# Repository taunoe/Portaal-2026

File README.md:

# Portaal

## Hardware

- PCB "Portaal"
- CH32V003F4P6 Board

## PCB "Portaal" Schematics

## Pins

|label|    name|connected|
|-----|--------|---------|
|    G|     GND|      GND|
|    O|Data Out|         |
|    R|        |     3.3V|
|    E|  Enable|      GND|
|    C|   Clock|      PC5|
|    L|    Lach|      PC1|
|    D| Data In|      PC6|
|    +|     VCC|     3.3V|

____
Tauno Erik 2026

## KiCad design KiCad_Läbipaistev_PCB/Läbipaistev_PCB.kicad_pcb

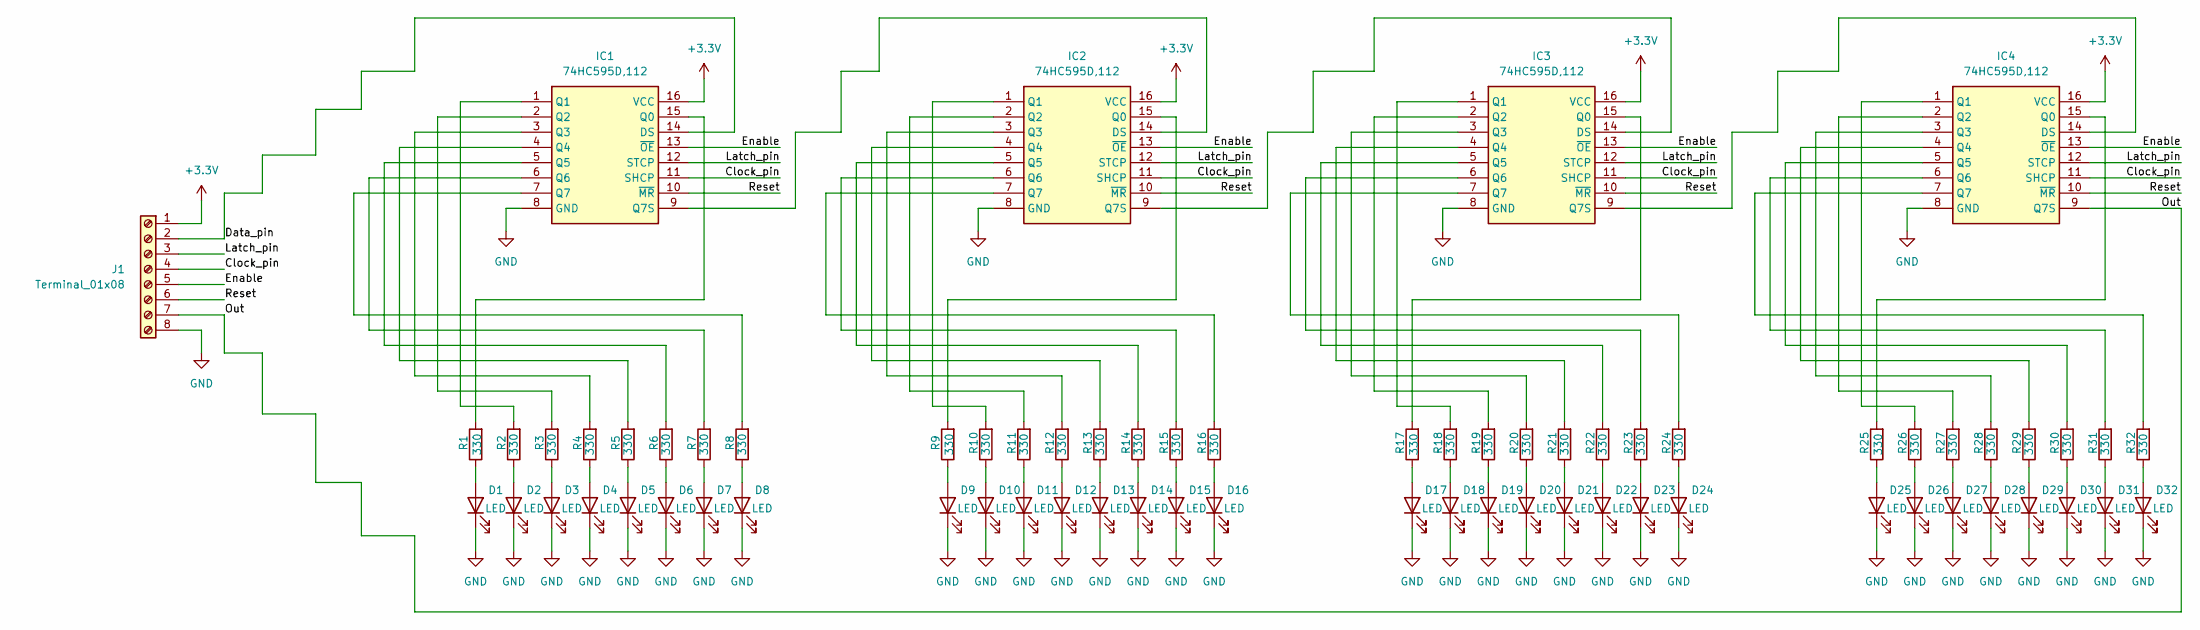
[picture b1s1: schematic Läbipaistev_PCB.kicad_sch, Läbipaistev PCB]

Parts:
D1, D2, D3, D4, D5, D6, D7, D8, D9, D10, D11, D12, D13, D14, D15, D16, D17, D18, D19, D20, D21, D22, D23, D24, D25, D26, D27, D28, D29, D30, D31, D32: LED; LED_1206_3216Metric
IC1, IC2, IC3, IC4: 74HC595D,112; tauno_SOIC127P600X175-16N; Manufacturer_Part_Number 74HC595D,112; Mouser Part Number 771-74HC595D
J1: Terminal_01x08; PinHeader_1x08_P2.54mm_Vertical
R1, R2, R3, R4, R5, R6, R7, R8, R9, R10, R11, R12, R13, R14, R15, R16, R17, R18, R19, R20, R21, R22, R23, R24, R25, R26, R27, R28, R29, R30, R31, R32: 330; R_1206_3216Metric_Pad1.30x1.75mm_HandSolder

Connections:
+3.3V: IC1.16 (VCC), IC2.16 (VCC), IC3.16 (VCC), IC4.16 (VCC), J1.1
/Clock_pin: IC1.11 (SHCP), IC2.11 (SHCP), IC3.11 (SHCP), IC4.11 (SHCP), J1.4
/Data_pin: IC1.14 (DS), J1.2
/Enable: IC1.13 (~OE), IC2.13 (~OE), IC3.13 (~OE), IC4.13 (~OE), J1.5
/Latch_pin: IC1.12 (STCP), IC2.12 (STCP), IC3.12 (STCP), IC4.12 (STCP), J1.3
/Out: IC4.9 (Q7S), J1.7
/Reset: IC1.10 (~MR), IC2.10 (~MR), IC3.10 (~MR), IC4.10 (~MR), J1.6
GND: D1.1 (K), D2.1 (K), D3.1 (K), D4.1 (K), D5.1 (K), D6.1 (K), D7.1 (K), D8.1 (K), D9.1 (K), D10.1 (K), D11.1 (K), D12.1 (K), D13.1 (K), D14.1 (K), D15.1 (K), D16.1 (K), D17.1 (K), D18.1 (K), D19.1 (K), D20.1 (K), D21.1 (K), D22.1 (K), D23.1 (K), D24.1 (K), D25.1 (K), D26.1 (K), D27.1 (K), D28.1 (K), D29.1 (K), D30.1 (K), D31.1 (K), D32.1 (K), IC1.8 (GND), IC2.8 (GND), IC3.8 (GND), IC4.8 (GND), J1.8
unnamed: D1.2 (A), R1.1
unnamed: D2.2 (A), R2.1
unnamed: D3.2 (A), R3.1
unnamed: D4.2 (A), R4.1
unnamed: D5.2 (A), R5.1
unnamed: D6.2 (A), R6.1
unnamed: D7.2 (A), R7.1
unnamed: D8.2 (A), R8.1
unnamed: D9.2 (A), R9.1
unnamed: D10.2 (A), R10.1
unnamed: D11.2 (A), R11.1
unnamed: D12.2 (A), R12.1
unnamed: D13.2 (A), R13.1
unnamed: D14.2 (A), R14.1
unnamed: D15.2 (A), R15.1
unnamed: D16.2 (A), R16.1
unnamed: D17.2 (A), R17.1
unnamed: D18.2 (A), R18.1
unnamed: D19.2 (A), R19.1
unnamed: D20.2 (A), R20.1
unnamed: D21.2 (A), R21.1
unnamed: D22.2 (A), R22.1
unnamed: D23.2 (A), R23.1
unnamed: D24.2 (A), R24.1
unnamed: D25.2 (A), R25.1
unnamed: D26.2 (A), R26.1
unnamed: D27.2 (A), R27.1
unnamed: D28.2 (A), R28.1
unnamed: D29.2 (A), R29.1
unnamed: D30.2 (A), R30.1
unnamed: D31.2 (A), R31.1
unnamed: D32.2 (A), R32.1
unnamed: IC1.15 (Q0), R1.2
unnamed: IC1.1 (Q1), R2.2
unnamed: IC1.2 (Q2), R3.2
unnamed: IC1.3 (Q3), R4.2
unnamed: IC1.4 (Q4), R5.2
unnamed: IC1.5 (Q5), R6.2
unnamed: IC1.6 (Q6), R7.2
unnamed: IC1.7 (Q7), R8.2
unnamed: IC1.9 (Q7S), IC2.14 (DS)
unnamed: IC2.15 (Q0), R9.2
unnamed: IC2.1 (Q1), R10.2
unnamed: IC2.2 (Q2), R11.2
unnamed: IC2.3 (Q3), R12.2
unnamed: IC2.4 (Q4), R13.2
unnamed: IC2.5 (Q5), R14.2
unnamed: IC2.6 (Q6), R15.2
unnamed: IC2.7 (Q7), R16.2
unnamed: IC2.9 (Q7S), IC3.14 (DS)
unnamed: IC3.15 (Q0), R17.2
unnamed: IC3.1 (Q1), R18.2
unnamed: IC3.2 (Q2), R19.2
unnamed: IC3.3 (Q3), R20.2
unnamed: IC3.4 (Q4), R21.2
unnamed: IC3.5 (Q5), R22.2
unnamed: IC3.6 (Q6), R23.2
unnamed: IC3.7 (Q7), R24.2
unnamed: IC3.9 (Q7S), IC4.14 (DS)
unnamed: IC4.15 (Q0), R25.2
unnamed: IC4.1 (Q1), R26.2
unnamed: IC4.2 (Q2), R27.2
unnamed: IC4.3 (Q3), R28.2
unnamed: IC4.4 (Q4), R29.2
unnamed: IC4.5 (Q5), R30.2
unnamed: IC4.6 (Q6), R31.2
unnamed: IC4.7 (Q7), R32.2

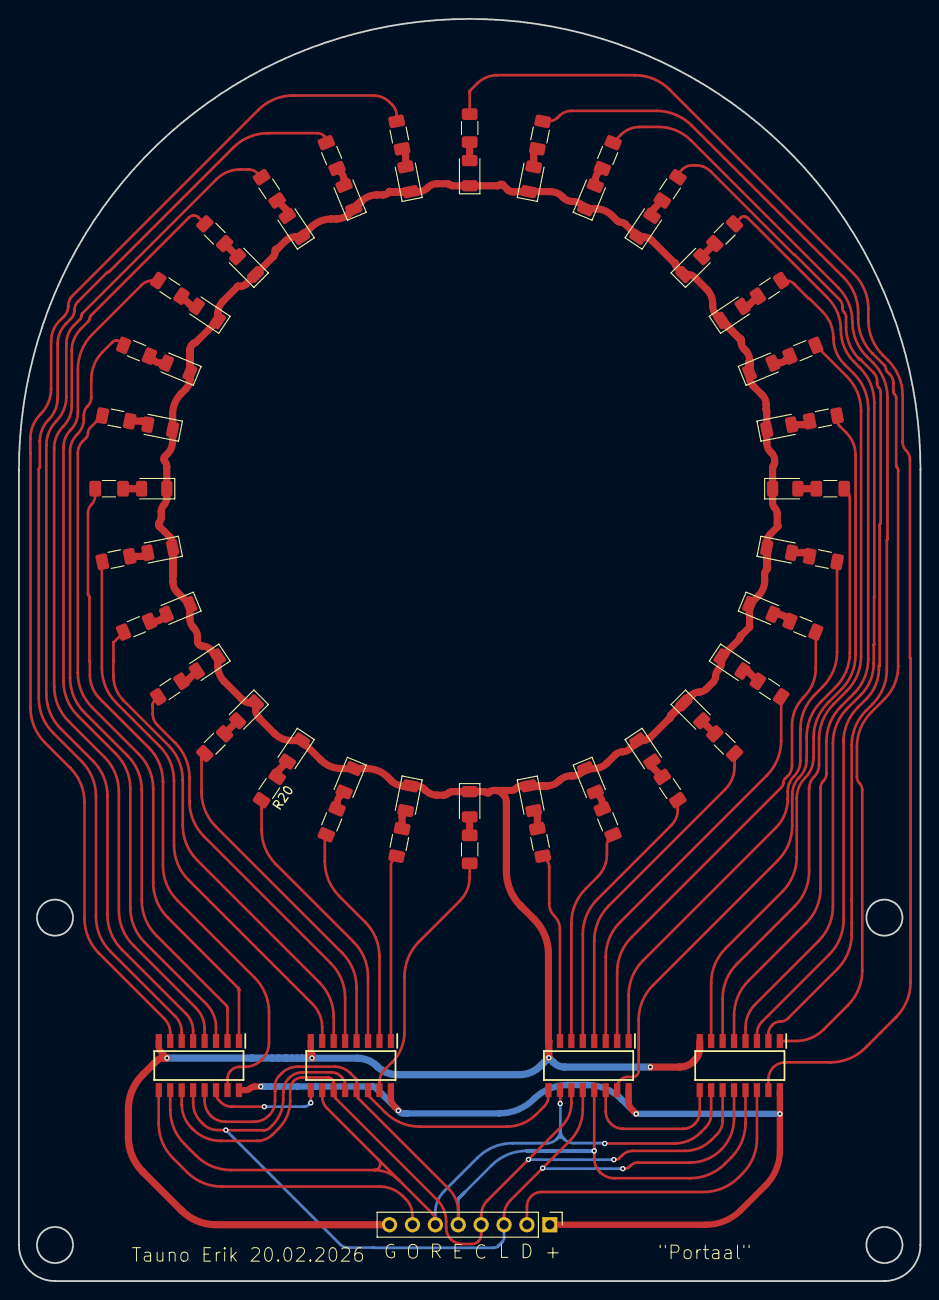
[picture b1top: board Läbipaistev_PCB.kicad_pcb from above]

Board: 2 copper layers, 100.0 x 140.0 mm, 69 parts (0 on the bottom side), 75 nets.

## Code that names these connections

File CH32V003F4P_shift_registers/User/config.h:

/********************************** (C) COPYRIGHT *******************************
 * File Name          : config
 * Author             : Tauno Erik
 * Version            : V1.0.0
 * Date               : 2026-11-03
 * Description        : Seaded
 *******************************************************************************/

// USART1
#define APP_BAUDRATE   115200

// Hardware SPI 1 pins - connected to Shift Registers
#define SPI1_PORT  GPIOC
#define DATA_PIN  GPIO_Pin_6 // MOSI
#define CLOCK_PIN GPIO_Pin_5 // SCK
#define LATCH_PIN GPIO_Pin_1



#define PATERN 0b111

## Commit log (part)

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2026-03-11 kicad
2026-03-11 [ImgBot] Optimize images
    *Total -- 324.49kb -> 284.84kb (12.22%)
    /img/renderdus/Läbipaistev_PCB.jpg -- 96.38kb -> 82.24kb (14.66%)
    /img/renderdus/Läbipaistev_PCB11.jpg -- 96.94kb -> 86.08kb (11.21%)
    /img/renderdus/Läbipaistev_PCB123.jpg -- 131.17kb -> 116.51kb (11.17%)
2026-03-12 imgs
2026-03-16 test code
